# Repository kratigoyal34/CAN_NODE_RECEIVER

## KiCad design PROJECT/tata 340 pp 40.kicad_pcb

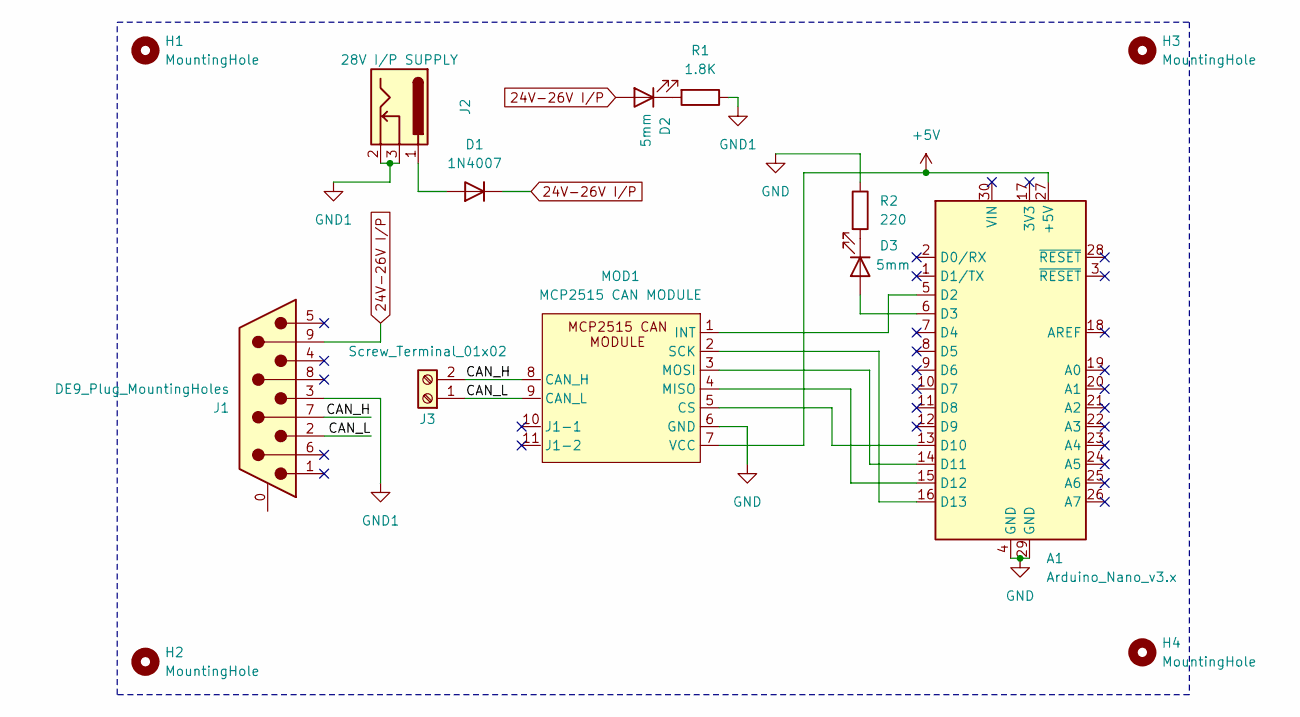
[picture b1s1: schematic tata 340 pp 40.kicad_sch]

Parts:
A1: Arduino_Nano_v3.x; Arduino_Nano
D1: 1N4007; D_DO-41_SOD81_P10.16mm_Horizontal
D2, D3: 5mm; LED_D5.0mm
H1, H2, H3, H4: MountingHole; MountingHole_3.2mm_M3
J1: DE9_Plug_MountingHoles; DSUB-9_Male_Horizontal_P2.77x2.84mm_EdgePinOffset7.70mm_Hou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
J2: 28V I/P SUPPLY; BarrelJack_Horizontal
J3: Screw_Terminal_01x02; TerminalBlock_Phoenix_MKDS-1,5-2_1x02_P5.00mm_Horizontal
MOD1: MCP2515 CAN MODULE
R1: 1.8K; R_Axial_DIN0207_L6.3mm_D2.5mm_P7.62mm_Horizontal
R2: 220; R_Axial_DIN0207_L6.3mm_D2.5mm_P7.62mm_Horizontal

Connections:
24V-26V I/P: D1.1 (K), D2.2 (A), J1.9
+5V: A1.27 (+5V), MOD1.7 (VCC)
/CAN_H: J1.7, J3.2, MOD1.8 (CAN_H)
/CAN_L: J1.2, J3.1, MOD1.9 (CAN_L)
GND: A1.4 (GND), A1.29 (GND), MOD1.6 (GND), R2.1
GND1: J1.3, J2.2, J2.3, R1.1
unnamed: A1.5 (D2), MOD1.1 (INT)
unnamed: A1.6 (D3), D3.2 (A)
unnamed: A1.13 (D10), MOD1.5 (CS)
unnamed: A1.14 (D11), MOD1.3 (MOSI)
unnamed: A1.15 (D12), MOD1.4 (MISO)
unnamed: A1.16 (D13), MOD1.2 (SCK)
unnamed: D1.2 (A), J2.1
unnamed: D2.1 (K), R1.2
unnamed: D3.1 (K), R2.2

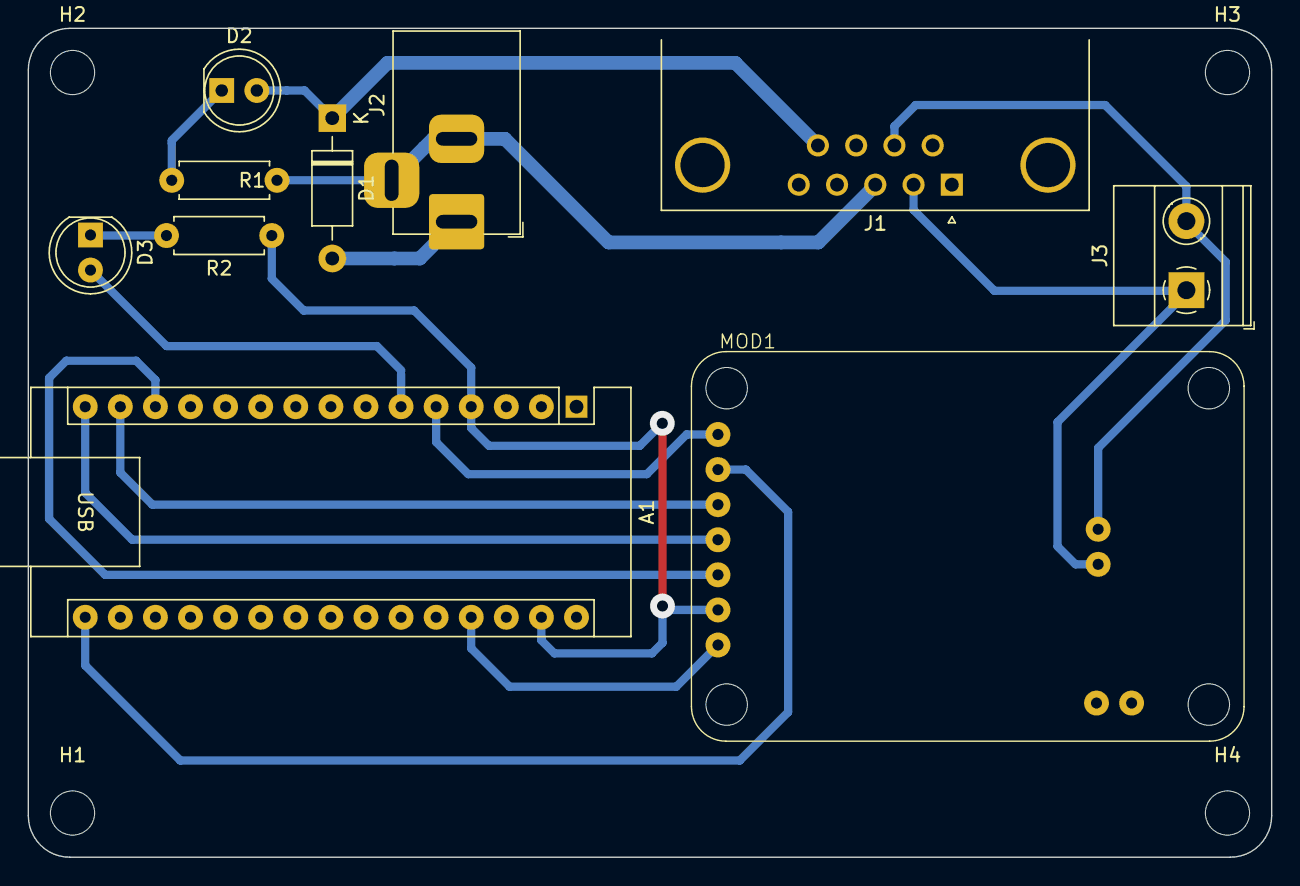
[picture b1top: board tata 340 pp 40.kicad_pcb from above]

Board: 2 copper layers, 90.0 x 60.0 mm, 14 parts (0 on the bottom side), 15 nets.

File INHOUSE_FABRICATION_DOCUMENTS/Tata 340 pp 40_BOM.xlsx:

Reference | Component | Value | Qty | DNP | Remark
A1 | Controller | Arduino_Nano_v3.x | 1 | DNP | Please place female headers for this component, please refer the attached scree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
D1 | diode | 1N4007 | 1
D2 | led | 5mm | 1
D3 | led | 5mm | 1
J1 | connector | DE9_Plug_MountingHoles | 1
J2 | connector | DC-JACK | 1
J3 | terminal | Screw_Terminal_01x02_5MM Pitch | 1
MOD1 | module | MCP2515 CAN MODULE | 1 | DNP | Please place female headers for this component, please refer the attached scree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
R1 | resistor | 1.8K | 1
R2 | resistor | 220R | 1
NA | female header | 2.54mm pitch header | As required |  | Please place these headers at DNP locations for mounting

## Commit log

2024-09-25 my pcb project
